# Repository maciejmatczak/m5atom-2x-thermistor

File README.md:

# m5atom-2x-thermistor
Simple temperature sensor based on M5 Atom.

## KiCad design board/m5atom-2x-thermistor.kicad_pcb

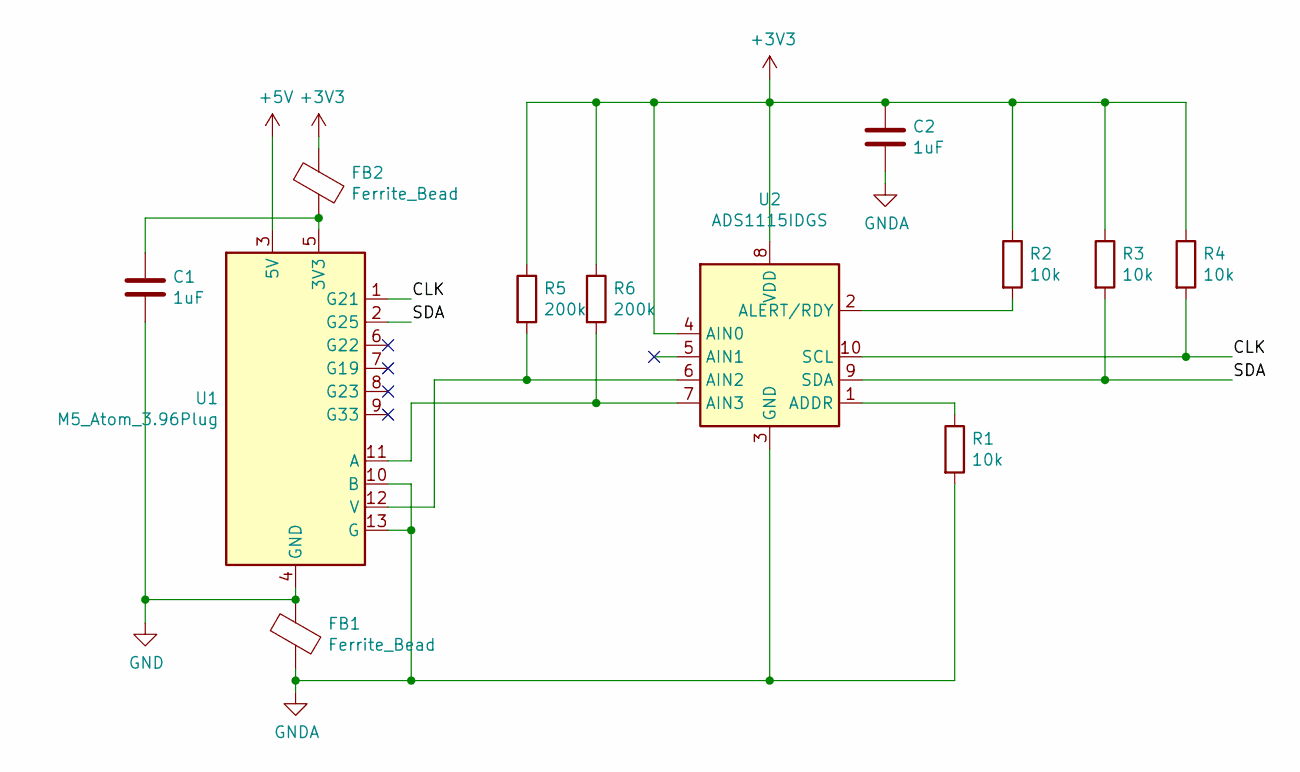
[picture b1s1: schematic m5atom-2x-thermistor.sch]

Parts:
C1, C2: 1uF; C_0805_2012Metric; LCSC Part C28323
FB1, FB2: Ferrite_Bead; R_0805_2012Metric; LCSC Part C1017
R1, R2, R3, R4: 10k; R_0805_2012Metric; LCSC Part C17414
R5, R6: 200k; R_Axial_DIN0204_L3.6mm_D1.6mm_P2.54mm_Vertical; JLCPCB BOM 0
U1: M5_Atom_3.96Plug; ProtoKit_3.96Plug; JLCPCB BOM 0
U2: ADS1115IDGS; TSSOP-10_3x3mm_P0.5mm; LCSC Part C37593

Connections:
+3V3: C2.1, FB2.1, R2.1, R3.1, R4.1, R5.1, R6.1, U2.4 (AIN0), U2.8 (VDD)
+5V: U1.3 (5V)
/CLK: R4.2, U1.1 (G21), U2.10 (SCL)
/SDA: R3.2, U1.2 (G25), U2.9 (SDA)
GND: C1.2, FB1.1, U1.4 (GND)
GNDA: C2.2, FB1.2, R1.2, U1.10 (B), U1.13 (G), U2.3 (GND)
unnamed: C1.1, FB2.2, U1.5 (3V3)
unnamed: R1.1, U2.1 (ADDR)
unnamed: R2.2, U2.2 (ALERT/RDY)
unnamed: R5.2, U1.12 (V), U2.6 (AIN2)
unnamed: R6.2, U1.11 (A), U2.7 (AIN3)

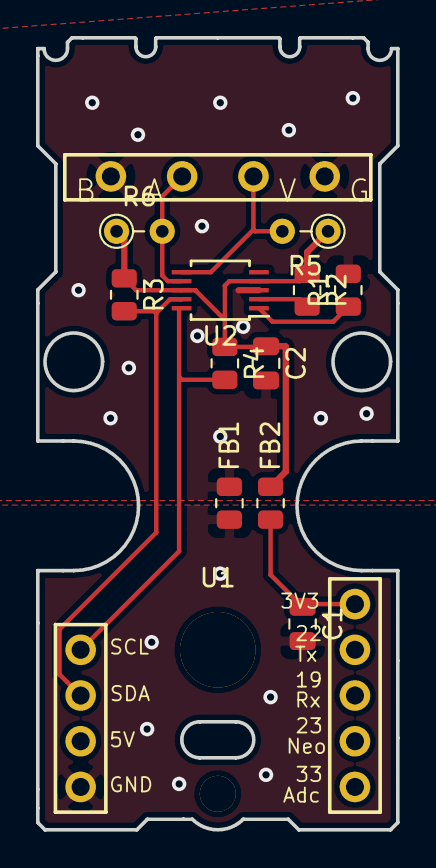
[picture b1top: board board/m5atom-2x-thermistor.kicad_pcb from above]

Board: 2 copper layers, 20.0 x 44.0 mm, 12 parts (0 on the bottom side), 10 nets.

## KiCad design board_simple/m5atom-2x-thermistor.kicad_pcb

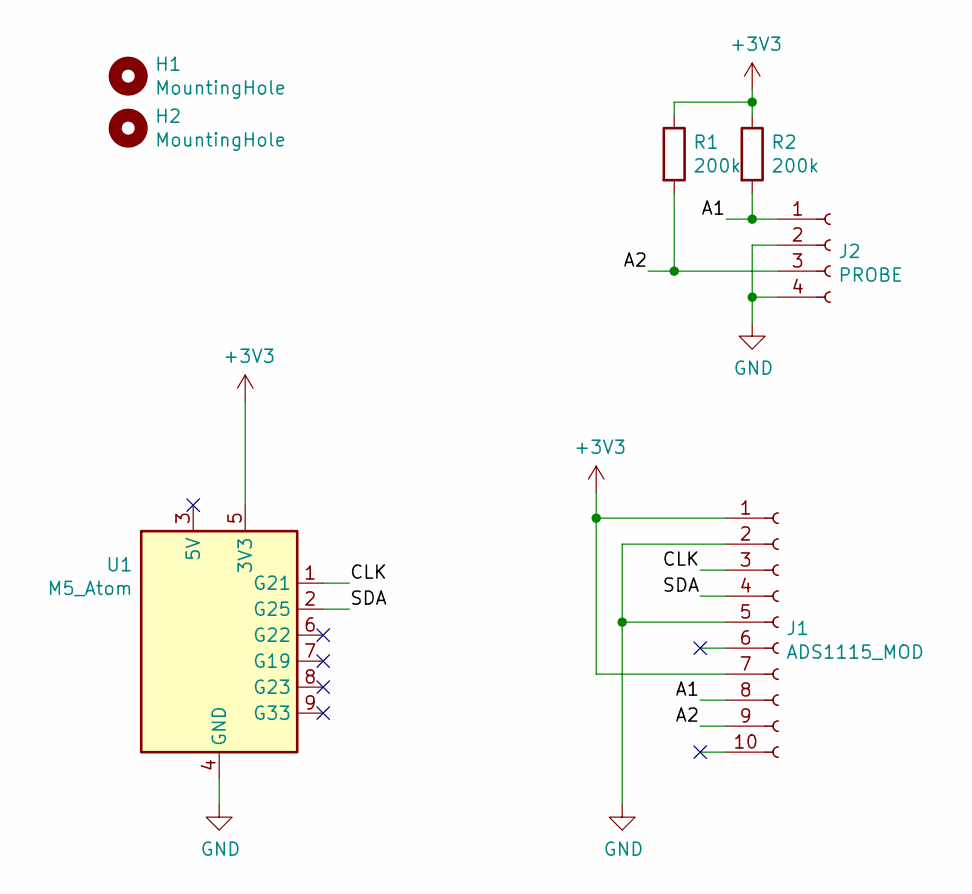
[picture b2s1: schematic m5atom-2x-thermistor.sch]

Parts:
H1, H2: MountingHole; MountingHole_2.7mm
J1: ADS1115_MOD; PinSocket_1x10_P2.54mm_Vertical
J2: PROBE; PinSocket_1x04_P2.54mm_Vertical
R1, R2: 200k; R_Axial_DIN0207_L6.3mm_D2.5mm_P10.16mm_Horizontal
U1: M5_Atom; JLCPCB BOM 0

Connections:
+3V3: J1.1, J1.7, R1.1, R2.1, U1.5 (3V3)
/A1: J1.8, J2.1, R2.2
/A2: J1.9, J2.3, R1.2
/CLK: J1.3, U1.1 (G21)
/SDA: J1.4, U1.2 (G25)
GND: J1.2, J1.5, J2.2, J2.4, U1.4 (GND)

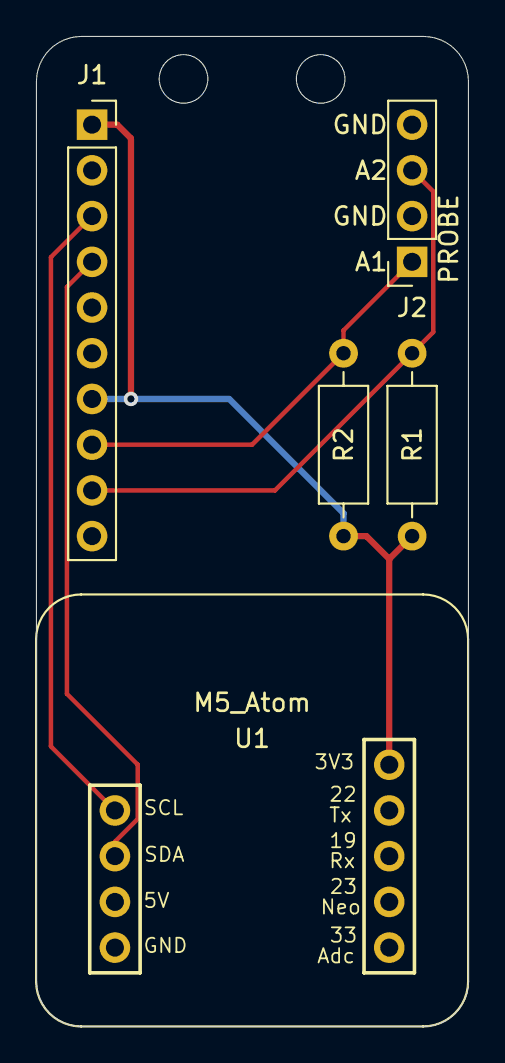
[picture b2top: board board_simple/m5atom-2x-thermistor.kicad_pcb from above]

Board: 2 copper layers, 24.0 x 55.0 mm, 7 parts (0 on the bottom side), 6 nets.

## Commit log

2021-01-31 Add M5 Atom KiCad library
2021-01-31 Checkout kicad-m5atom-library to 0.0.1-rc2
2021-01-31 Change m5 atom lib to rc3
2021-01-31 To rc4...
2021-02-13 Change to rc5
2021-02-14 add kicad jlcpcb bom plugin submodule
2021-02-14 add initial design
2022-05-29 New simple board, introducing mess in submodule...
2022-05-29 Change Makefile to use board_simple
